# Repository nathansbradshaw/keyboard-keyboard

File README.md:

# Keyboard-keyboard

Keyboard-keyboard is a Hall-effect keyboard PCB. The design is based on the IBM Model M keyboard layout. But this is intended to be used as a gimicky musical keyboard.

## Acknowledgements

- Based on the work of 
  [peppapighs](https://github.com/peppapighs/HE60/tree/main) for the hall effect keyboard and [dcpedit](https://github.com/dcpedit/mod-mmm) for the Model M layout.

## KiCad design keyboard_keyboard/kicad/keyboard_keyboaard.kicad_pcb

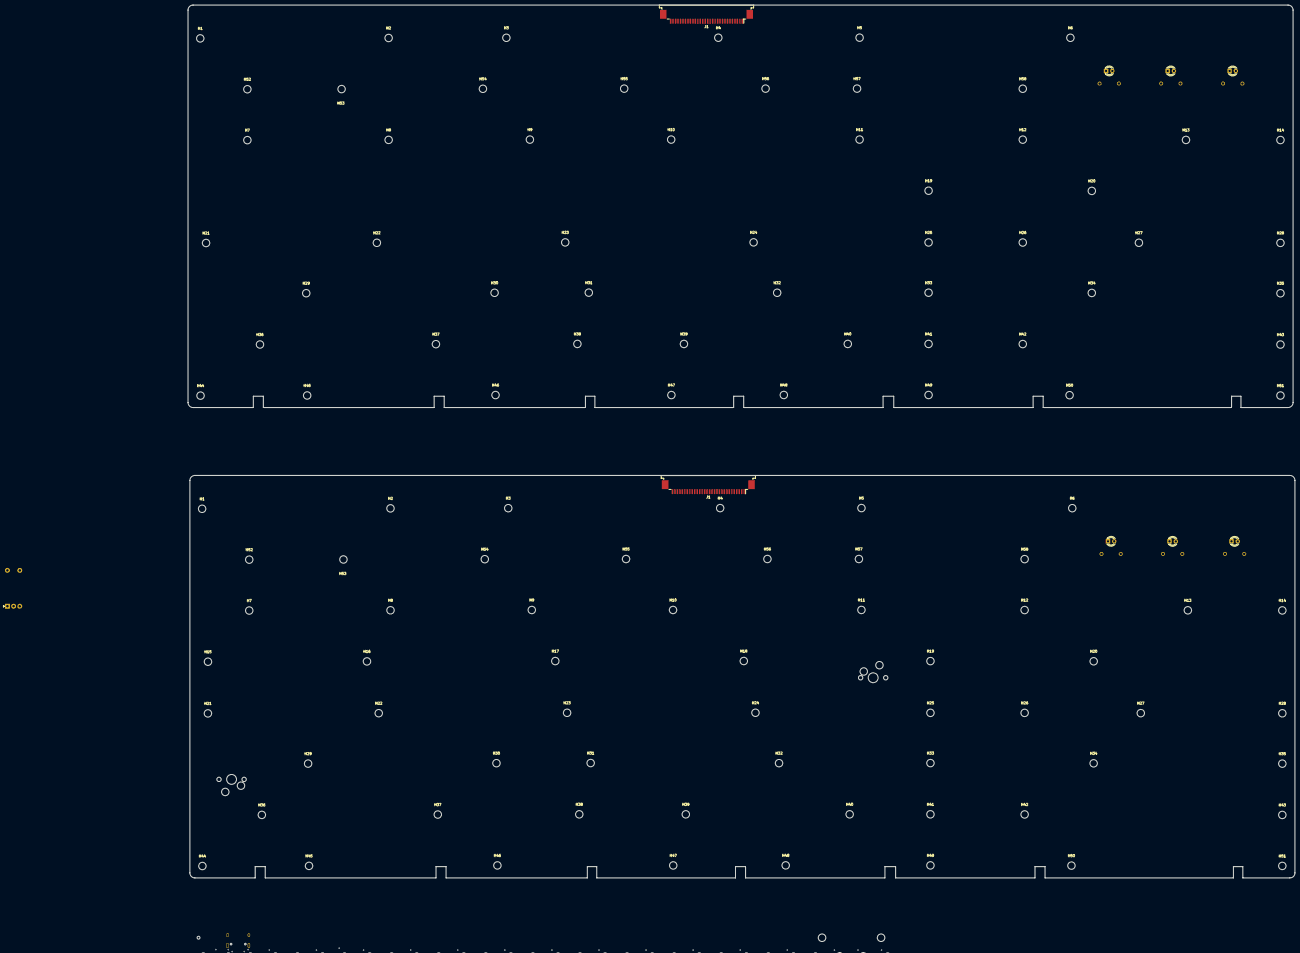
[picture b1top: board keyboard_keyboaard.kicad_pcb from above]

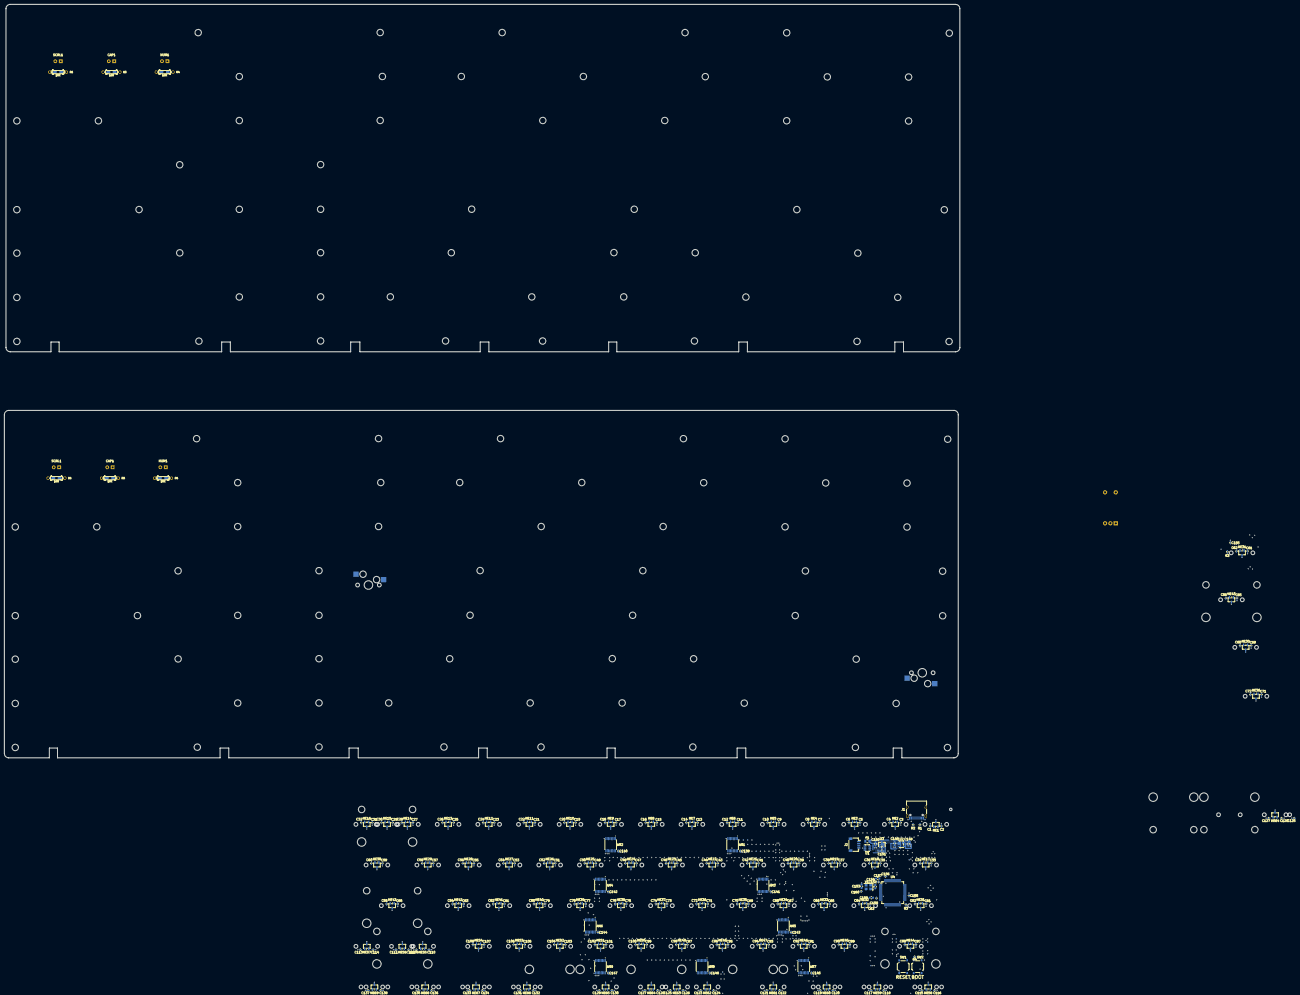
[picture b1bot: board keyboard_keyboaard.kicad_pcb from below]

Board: 2 copper layers, 447.8 x 353.1 mm, 484 parts (270 on the bottom side), 128 nets, no tracks yet.

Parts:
AM1, AM2, AM3, AM4, AM5, AM6, AM7, AM8, AM9: SN74LV4051A; TSSOP-16_4.4x5mm_P0.65mm
C1, C3, C5, C7, C9, C11, C13, C15, C17, C19, C21, C23, C25, C27, C29, C31, C33, C35, C37, C39, C41, C43, C45, C47, C49, C51, C53, C55, C57, C59, C59#2, C61, C61#2, C63, C65, C67, C69, C71, C71#2, C73, C75, C77, C79, C81, C83, C85, C85#2, C87, C89, C91, C93, C95, C97, C99, C101, C103, C105, C107, C109, C111, C113, C115, C117, C119, C121, C123, C125, C125#2, C127, C127#2, C129, C131, C133, C135, C137, C139, C140, C141, C142, C143, C144, C145, C146, C147, C154, C155, C155#2, C156, C158, C160: 100n; C_0402_1005Metric
C2, C4, C6, C8, C10, C12, C14, C16, C18, C20, C22, C24, C26, C28, C30, C32, C34, C36, C38, C40, C42, C44, C46, C48, C50, C52, C54, C56, C58, C60, C60#2, C62, C62#2, C64, C66, C68, C70, C72, C72#2, C74, C76, C78, C80, C82, C84, C86, C86#2, C88, C90, C92, C94, C96, C98, C100, C102, C104, C106, C108, C110, C112, C114, C116, C118, C120, C122, C124, C126, C128, C128#2, C130, C132, C134, C136, C138: 4.7n; C_0402_1005Metric
C148, C149, C150, C151: 2.2u; C_0603_1608Metric
C152, C153: 30p; C_0603_1608Metric
C157: 10u; C_0603_1608Metric
C159: 1u; C_0603_1608Metric
CAP1, CAP1#2: LED; LED_D3.0mm
F1: BSMD0805-050-24V; Fuse_0805_2012Metric
H1, H1#2, H2, H2#2, H3, H3#2, H4, H4#2, H5, H5#2, H6, H6#2, H7, H7#2, H8, H8#2, H9, H9#2, H10, H10#2, H11, H11#2, H12, H12#2, H13, H13#2, H14, H14#2, H15, H16, H17, H18, H19, H19#2, H20, H20#2, H21, H21#2, H22, H22#2, H23, H23#2, H24, H24#2, H25, H25#2, H26, H26#2, H27, H27#2, H28, H28#2, H29, H29#2, H30, H30#2, H31, H31#2, H32, H32#2, H33, H33#2, H34, H34#2, H35, H35#2, H36, H36#2, H37, H37#2, H38, H38#2, H39, H39#2, H40, H40#2, H41, H41#2, H42, H42#2, H43, H43#2, H44, H44#2, H45, H45#2, H46, H46#2, H47, H47#2, H48, H48#2, H49, H49#2, H50, H50#2, H51, H51#2, H52, H52#2, H53, H53#2, H54, H54#2, H55, H55#2, H56, H56#2, H57, H57#2, H58, H58#2: MountingHole; MountingHole_3mm
HE1, HE2, HE3, HE4, HE5, HE6, HE7, HE8, HE9, HE10, HE11, HE12, HE13, HE14, HE15, HE16, HE17, HE18, HE19, HE20, HE21, HE22, HE23, HE24, HE25, HE26, HE27, HE28, HE29, HE30, HE30#2, HE31, HE31#2, HE32, HE33, HE34, HE35, HE36, HE36#2, HE37, HE38, HE39, HE40, HE41, HE42, HE43, HE43#2, HE44, HE45, HE46, HE47, HE48, HE49, HE50, HE51, HE52, HE53, HE54, HE55, HE56, HE57, HE58, HE59, HE60, HE61, HE62, HE63, HE64, HE64#2, HE65, HE66, HE67, HE68, HE69: MT9102ET; SOT-23-3
J1, J1#2: Conn_01x30; TE_3-84952-0_1x30-1MP_P1.0mm_Horizontal
J1#3: TYPE-C-31-M-12; USB_C_Receptacle_HRO_TYPE-C-31-M-12
J2: JST_SH; JST_SH_SM04B-SRSS-TB_1x04-1MP_P1.00mm_Horizontal
MX1, MX2, MX3, MX4, MX5, MX6, MX7, MX8, MX9, MX10, MX11, MX12, MX13, MX14, MX16, MX18, MX19, MX20, MX21, MX22, MX23, MX24, MX25, MX26, MX27, MX28, MX29, MX32, MX33, MX34, MX35, MX36, MX36#2, MX37, MX38, MX39, MX40, MX41, MX42, MX45, MX46, MX47, MX48, MX49, MX50, MX51, MX52, MX53, MX54, MX57, MX61, MX64, MX69, MX73: 1U; MX-1U
MX15: 2U; MX-2U
MX17, MX30, MX30#2, MX59, MX63, MX71, MX75: 1.5U; MX-1.5U
MX31, MX31#2, MX55: 1.75U; MX-1.75U
MX040: MX-NoLED; MXOnly-1.25U-Hotswap
MX43, MX43#2, MX44: 2.25U; MX-2.25U
MX56: 2.75U; MX-2.75U
MX58, MX60, MX62, MX70, MX72, MX74, MX76: 1.25U; MX-1.25U
MX65: 2.25U; MX-2.25U-ReversedStabilizers
MX66, MX66#2: 6.25U; MX-6.25U-ReversedStabilizers
MX67, MX67#2: 7U; MX-7U-ReversedStabilizers
MX68, MX68#2: 2.75U; MX-2.75U-ReversedStabilizers
MX086: MX-NoLED; MXOnly-1.5U-Hotswap
NUM1, NUM1#2: LED; LED_D3.0mm
R1, R2: 5.1k; R_0402_1005Metric
R3, R3#2, R4#3: 12k; R_0402_1005Metric
R4, R4#2, R5, R5#2, R6, R6#2: 10K; Resistor-Hybrid-Back
SCRL1, SCRL1#2: LED; LED_D3.0mm
SW1, SW2: TS-1187A-B-A-B; SW_Push_1P1T_XKB_TS-1187A
SWR3: RotaryEncoder_Switch; RotaryEncoder_EC11_Nonplated
TH1, TH2: ToolingHole
U1: USBLC6-2SC6; SOT-23-6
U2: TLV75733PDBV; SOT-23-5
U3: XC6206P332MR-G; SOT-23-3
U4: AT32F405RCT7; LQFP-64_10x10mm_P0.5mm
Y1: X322512MSB4SI; Crystal_SMD_3225-4Pin_3.2x2.5mm

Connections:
+3.3V: C151.1, C154.1, C155.1, C155#2.1, C156.1, C157.1, SW2.2, U3.2 (VO), U4.1 (VDD), U4.36 (VDD), U4.64 (VDD)
+3.3VA: AM1.16 (VDD), AM2.16 (VDD), AM3.16 (VDD), AM4.16 (VDD), AM5.16 (VDD), AM6.16 (VDD), AM7.16 (VDD), AM8.16 (VDD), AM9.16 (VDD), C1.1, C3.1, C5.1, C7.1, C9.1, C11.1, C13.1, C15.1, C17.1, C19.1, C21.1, C23.1, C25.1, C27.1, C29.1, C31.1, C33.1, C35.1, C37.1, C39.1, C41.1, C43.1, C45.1, C47.1, C49.1, C51.1, C53.1, C55.1, C57.1, C59.1, C59#2.1, C61.1, C61#2.1, C63.1, C65.1, C67.1, C69.1, C71.1, C71#2.1, C73.1, C75.1, C77.1, C79.1, C81.1, C83.1, C85.1, C85#2.1, C87.1, C89.1, C91.1, C93.1, C95.1, C97.1, C99.1, C101.1, C103.1, C105.1, C107.1, C109.1, C111.1, C113.1, C115.1, C117.1, C119.1, C121.1, C123.1, C125.1, C125#2.1, C127.1, C127#2.1, C129.1, C131.1, C133.1, C135.1, C137.1, C139.1, C140.1, C141.1, C142.1, C143.1, C144.1, C145.1, C146.1, C147.1, C149.1, C158.1, C159.1, HE1.1 (VCC), HE2.1 (VCC), HE3.1 (VCC), HE4.1 (VCC), HE5.1 (VCC), HE6.1 (VCC), HE7.1 (VCC), HE8.1 (VCC), HE9.1 (VCC), HE10.1 (VCC), HE11.1 (VCC), HE12.1 (VCC), HE13.1 (VCC), HE14.1 (VCC), HE15.1 (VCC), HE16.1 (VCC), HE17.1 (VCC), HE18.1 (VCC), HE19.1 (VCC), HE20.1 (VCC), HE21.1 (VCC), HE22.1 (VCC), HE23.1 (VCC), HE24.1 (VCC), HE25.1 (VCC), HE26.1 (VCC), HE27.1 (VCC), HE28.1 (VCC), HE29.1 (VCC), HE30.1 (VCC), HE30#2.1 (VCC), HE31.1 (VCC), HE31#2.1 (VCC), HE32.1 (VCC), HE33.1 (VCC), HE34.1 (VCC), HE35.1 (VCC), HE36.1 (VCC), HE36#2.1 (VCC), HE37.1 (VCC), HE38.1 (VCC), HE39.1 (VCC), HE40.1 (VCC), HE41.1 (VCC), HE42.1 (VCC), HE43.1 (VCC), HE43#2.1 (VCC), HE44.1 (VCC), HE45.1 (VCC), HE46.1 (VCC), HE47.1 (VCC), HE48.1 (VCC), HE49.1 (VCC), HE50.1 (VCC), HE51.1 (VCC), HE52.1 (VCC), HE53.1 (VCC), HE54.1 (VCC), HE55.1 (VCC), HE56.1 (VCC), HE57.1 (VCC), HE58.1 (VCC), HE59.1 (VCC), HE60.1 (VCC), HE61.1 (VCC), HE62.1 (VCC), HE63.1 (VCC), HE64.1 (VCC), HE64#2.1 (VCC), HE65.1 (VCC), HE66.1 (VCC), HE67.1 (VCC), HE68.1 (VCC), HE69.1 (VCC), U2.5 (OUT), U4.13 (VDDA)
+5V: C148.1, C150.1, F1.2, U1.5 (VBUS), U2.1 (IN), U2.3 (EN), U3.3 (VI)
BOOT0: R4#3.1, SW2.1, U4.60 (PF11/BOOT0)
CAPS_LED: CAP1.2 (A), CAP1#2.2 (A), J1.29, J1#2.29
COL0: J1.28, J1#2.28, MX040.1 (COL)
COL1: J1.27, J1#2.27
COL2: J1.26, J1#2.26
COL3: J1.23, J1#2.23
COL4: J1.22, J1#2.22
COL5: J1.11, J1#2.11
COL6: J1.10, J1#2.10, MX086.1 (COL)
COL7: J1.7, J1#2.7
COL8: J1.5, J1#2.5
COL9: J1.4, J1#2.4
GND: AM1.6 (Inh), AM1.7 (VEE), AM1.8 (VSS), AM1.12 (X3), AM2.6 (Inh), AM2.7 (VEE), AM2.8 (VSS), AM3.2 (X6), AM3.6 (Inh), AM3.7 (VEE), AM3.8 (VSS), AM4.6 (Inh), AM4.7 (VEE), AM4.8 (VSS), AM5.6 (Inh), AM5.7 (VEE), AM5.8 (VSS), AM5.15 (X2), AM6.6 (Inh), AM6.7 (VEE), AM6.8 (VSS), AM7.6 (Inh), AM7.7 (VEE), AM7.8 (VSS), AM8.6 (Inh), AM8.7 (VEE), AM8.8 (VSS), AM9.6 (Inh), AM9.7 (VEE), AM9.8 (VSS), C1.2, C2.2, C3.2, C4.2, C5.2, C6.2, C7.2, C8.2, C9.2, C10.2, C11.2, C12.2, C13.2, C14.2, C15.2, C16.2, C17.2, C18.2, C19.2, C20.2, C21.2, C22.2, C23.2, C24.2, C25.2, C26.2, C27.2, C28.2, C29.2, C30.2, C31.2, C32.2, C33.2, C34.2, C35.2, C36.2, C37.2, C38.2, C39.2, C40.2, C41.2, C42.2, C43.2, C44.2, C45.2, C46.2, C47.2, C48.2, C49.2, C50.2, C51.2, C52.2, C53.2, C54.2, C55.2, C56.2, C57.2, C58.2, C59.2, C59#2.2, C60.2, C60#2.2, C61.2, C61#2.2, C62.2, C62#2.2, C63.2, C64.2, C65.2, C66.2, C67.2, C68.2, C69.2, C70.2, C71.2, C71#2.2, C72.2, C72#2.2, C73.2, C74.2, C75.2, C76.2, C77.2, C78.2, C79.2, C80.2, C81.2, C82.2, C83.2, C84.2, C85.2, C85#2.2, C86.2, C86#2.2, C87.2, C88.2, C89.2, C90.2, C91.2, C92.2, C93.2, C94.2, C95.2, C96.2, C97.2, C98.2, C99.2, C100.2, C101.2, C102.2, C103.2, C104.2, C105.2, C106.2, C107.2, C108.2, C109.2, C110.2, C111.2, C112.2, C113.2, C114.2, C115.2, C116.2, C117.2, C118.2, C119.2, C120.2, C121.2, C122.2, C123.2, C124.2, C125.2, C125#2.2, C126.2, C127.2, C127#2.2, C128.2, C128#2.2, C129.2, C130.2, C131.2, C132.2, C133.2, C134.2, C135.2, C136.2, C137.2, C138.2, C139.2, C140.2, C141.2, C142.2, C143.2, C144.2, C145.2, C146.2, C147.2, C148.2, C149.2, C150.2, C151.2, C152.2, C153.2, C154.2, C155.2, C155#2.2, C156.2, C157.2, C158.2, C159.2, C160.2, HE1.3 (GND), HE2.3 (GND), HE3.3 (GND), HE4.3 (GND), HE5.3 (GND), HE6.3 (GND), HE7.3 (GND), HE8.3 (GND), HE9.3 (GND), HE10.3 (GND), HE11.3 (GND), HE12.3 (GND), HE13.3 (GND), HE14.3 (GND), HE15.3 (GND), HE16.3 (GND), HE17.3 (GND), HE18.3 (GND), HE19.3 (GND), HE20.3 (GND), HE21.3 (GND), HE22.3 (GND), HE23.3 (GND), HE24.3 (GND), HE25.3 (GND), HE26.3 (GND), HE27.3 (GND), HE28.3 (GND), HE29.3 (GND), HE30.3 (GND), HE30#2.3 (GND), HE31.3 (GND), HE31#2.3 (GND), HE32.3 (GND), HE33.3 (GND), HE34.3 (GND), HE35.3 (GND), HE36.3 (GND), HE36#2.3 (GND), HE37.3 (GND), HE38.3 (GND), HE39.3 (GND), HE40.3 (GND), HE41.3 (GND), HE42.3 (GND), HE43.3 (GND), HE43#2.3 (GND), HE44.3 (GND), HE45.3 (GND), HE46.3 (GND), HE47.3 (GND), HE48.3 (GND), HE49.3 (GND), HE50.3 (GND), HE51.3 (GND), HE52.3 (GND), HE53.3 (GND), HE54.3 (GND), HE55.3 (GND), HE56.3 (GND), HE57.3 (GND), HE58.3 (GND), HE59.3 (GND), HE60.3 (GND), HE61.3 (GND), HE62.3 (GND), HE63.3 (GND), HE64.3 (GND), HE64#2.3 (GND), HE65.3 (GND), HE66.3 (GND), HE67.3 (GND), HE68.3 (GND), HE69.3 (GND), J1.1, J1.30, J1#2.1, J1#2.30, J1#3.A1 (GND), J1#3.A12 (GND), J1#3.B1 (GND), J1#3.B12 (GND), J1#3.S1 (SHIELD), J2.4, R1.2, R2.1, R3.1, R3#2.1, R4.2, R4#2.2, R4#3.2, R5.2, R5#2.2, R6.2, R6#2.2, SW1.2, U1.2 (GND), U2.2 (GND), U3.1 (GND), U4.12 (VSSA), U4.31 (VSS), U4.63 (VSS), Y1.2, Y1.4
HE1: AM3.15 (X2), C2.1, HE1.2 (OUT)
HE2: AM1.15 (X2), C4.1, HE2.2 (OUT)
HE3: AM1.14 (X1), C6.1, HE3.2 (OUT)
HE4: AM1.13 (X0), C8.1, HE4.2 (OUT)
HE5: AM1.1 (X4), C10.1, HE5.2 (OUT)
HE6: AM1.2 (X6), C12.1, HE6.2 (OUT)
HE7: AM1.4 (X7), C14.1, HE7.2 (OUT)
HE8: AM1.5 (X5), C16.1, HE8.2 (OUT)
HE9: AM2.1 (X4), C18.1, HE9.2 (OUT)
HE10: AM2.2 (X6), C20.1, HE10.2 (OUT)
HE11: AM2.4 (X7), C22.1, HE11.2 (OUT)
HE12: AM2.5 (X5), C24.1, HE12.2 (OUT)
HE13: AM2.15 (X2), C26.1, HE13.2 (OUT)
HE14: AM2.14 (X1), C28.1, HE14.2 (OUT)
HE15: AM2.13 (X0), C30.1, HE15.2 (OUT)
HE16: AM2.12 (X3), C32.1, HE16.2 (OUT)
HE17: AM3.14 (X1), C34.1, HE17.2 (OUT)
HE18: AM3.13 (X0), C36.1, HE18.2 (OUT)
HE19: AM3.12 (X3), C38.1, HE19.2 (OUT)
HE20: AM3.1 (X4), C40.1, HE20.2 (OUT)
HE21: AM3.4 (X7), C42.1, HE21.2 (OUT)
HE22: AM3.5 (X5), C44.1, HE22.2 (OUT)
HE23: AM4.1 (X4), C46.1, HE23.2 (OUT)
HE24: AM4.2 (X6), C48.1, HE24.2 (OUT)
HE25: AM4.4 (X7), C50.1, HE25.2 (OUT)
HE26: AM4.5 (X5), C52.1, HE26.2 (OUT)
HE27: AM4.15 (X2), C54.1, HE27.2 (OUT)
HE28: AM4.14 (X1), C56.1, HE28.2 (OUT)
HE29: AM4.13 (X0), C58.1, HE29.2 (OUT)
HE30: AM4.12 (X3), C60.1, C60#2.1, HE30.2 (OUT), HE30#2.2 (OUT)
HE31: AM7.1 (X4), C62.1, C62#2.1, HE31.2 (OUT), HE31#2.2 (OUT)
HE32: AM5.1 (X4), C64.1, HE32.2 (OUT)
HE33: AM5.2 (X6), C66.1, HE33.2 (OUT)
HE34: AM5.4 (X7), C68.1, HE34.2 (OUT)
HE35: AM5.5 (X5), C70.1, HE35.2 (OUT)
HE36: AM5.14 (X1), C72.1, C72#2.1, HE36.2 (OUT), HE36#2.2 (OUT)
HE37: AM5.13 (X0), C74.1, HE37.2 (OUT)
HE38: AM5.12 (X3), C76.1, HE38.2 (OUT)
HE39: AM6.1 (X4), C78.1, HE39.2 (OUT)
HE40: AM6.2 (X6), C80.1, HE40.2 (OUT)
HE41: AM6.4 (X7), C82.1, HE41.2 (OUT)
HE42: AM6.5 (X5), C84.1, HE42.2 (OUT)
HE43: AM6.15 (X2), C86.1, C86#2.1, HE43.2 (OUT), HE43#2.2 (OUT)
HE44: AM7.2 (X6), C88.1, HE44.2 (OUT)
HE45: AM7.4 (X7), C90.1, HE45.2 (OUT)
HE46: AM7.5 (X5), C92.1, HE46.2 (OUT)
HE47: AM8.1 (X4), C94.1, HE47.2 (OUT)
HE48: AM8.2 (X6), C96.1, HE48.2 (OUT)
HE49: AM8.4 (X7), C98.1, HE49.2 (OUT)
HE50: AM8.5 (X5), C100.1, HE50.2 (OUT)
HE51: AM9.1 (X4), C102.1, HE51.2 (OUT)
HE52: AM9.2 (X6), C104.1, HE52.2 (OUT)
HE53: AM9.4 (X7), C106.1, HE53.2 (OUT)
HE54: AM9.5 (X5), C108.1, HE54.2 (OUT)
HE55: AM6.12 (X3), C110.1, HE55.2 (OUT)
HE56: AM6.13 (X0), C112.1, HE56.2 (OUT)
HE57: AM6.14 (X1), C114.1, HE57.2 (OUT)
HE58: AM7.15 (X2), C116.1, HE58.2 (OUT)
HE59: AM7.14 (X1), C118.1, HE59.2 (OUT)
HE60: AM7.13 (X0), C120.1, HE60.2 (OUT)
HE61: AM7.12 (X3), C122.1, HE61.2 (OUT)
HE62: AM8.12 (X3), C124.1, HE62.2 (OUT)
HE63: AM8.13 (X0), C126.1, HE63.2 (OUT)
HE64: AM8.14 (X1), C128.1, C128#2.1, HE64.2 (OUT), HE64#2.2 (OUT)
HE65: AM8.15 (X2), C130.1, HE65.2 (OUT)
HE66: AM9.12 (X3), C132.1, HE66.2 (OUT)
HE67: AM9.13 (X0), C134.1, HE67.2 (OUT)
HE68: AM9.14 (X1), C136.1, HE68.2 (OUT)
HE69: AM9.15 (X2), C138.1, HE69.2 (OUT)
HEXT_IN: C152.1, U4.5 (PF0/HEXT_IN), Y1.1
HEXT_OUT: C153.1, U4.6 (PF1/HEXT_OUT), Y1.3
MUX_OUT_1: AM1.3 (X), U4.17 (PA3)
MUX_OUT_2: AM2.3 (X), U4.20 (PA4)
MUX_OUT_3: AM3.3 (X), U4.21 (PA5)
MUX_OUT_4: AM4.3 (X), U4.22 (PA6)
MUX_OUT_5: AM5.3 (X), U4.23 (PA7)
MUX_OUT_6: AM6.3 (X), U4.24 (PC4)
MUX_OUT_7: AM7.3 (X), U4.25 (PC5)
MUX_OUT_8: AM8.3 (X), U4.26 (PB0)
MUX_OUT_9: AM9.3 (X), U4.27 (PB1)
MUX_SELECT_0: AM1.11 (A), AM2.11 (A), AM3.11 (A), AM4.11 (A), AM5.11 (A), AM6.11 (A), AM7.11 (A), AM8.11 (A), AM9.11 (A), U4.9 (PC1)
MUX_SELECT_1: AM1.10 (B), AM2.10 (B), AM3.10 (B), AM4.10 (B), AM5.10 (B), AM6.10 (B), AM7.10 (B), AM8.10 (B), AM9.10 (B), U4.10 (PC2)
MUX_SELECT_2: AM1.9 (C), AM2.9 (C), AM3.9 (C), AM4.9 (C), AM5.9 (C), AM6.9 (C), AM7.9 (C), AM8.9 (C), AM9.9 (C), U4.11 (PC3)
NRST: C160.1, SW1.1, U4.7 (NRST)
NUM_LED: J1.3, J1#2.3, NUM1.2 (A), NUM1#2.2 (A)
unnamed: CAP1.1 (K), CAP1#2.1 (K), R5.1, R5#2.1
unnamed: J1#3.A5 (CC1), R1.1
unnamed: J1#3.B5 (CC2), R2.2
unnamed: NUM1.1 (K), NUM1#2.1 (K), R4.1, R4#2.1
unnamed: R6.1, R6#2.1, SCRL1.1 (K), SCRL1#2.1 (K)
unnamed: R3.2, R3#2.2, U4.33 (OTGHS1_R)
RE1: J1.9, J1#2.9
RE2: J1.8, J1#2.8
RE3: J1.6, J1#2.6
ROW0: J1.25, J1#2.25
ROW1: J1.21, J1#2.21
ROW2: J1.20, J1#2.20
ROW3: J1.19, J1#2.19
ROW4: J1.18, J1#2.18
ROW5: J1.17, J1#2.17
ROW6: J1.24, J1#2.24
ROW7: J1.16, J1#2.16
ROW8: J1.15, J1#2.15
ROW9: J1.14, J1#2.14
ROW10: J1.13, J1#2.13
ROW11: J1.12, J1#2.12
SCRL_LED: J1.2, J1#2.2, SCRL1.2 (A), SCRL1#2.2 (A)
USB_D+: U1.4 (I/O2), U4.35 (OTGHS1_D+)
USB_D-: U1.6 (I/O1), U4.34 (OTGHS1_D-)
USB_PLUG_D+: J1#3.A6 (D+), J1#3.B6 (D+), J2.3, U1.3 (I/O2)
USB_PLUG_D-: J1#3.A7 (D-), J1#3.B7 (D-), J2.2, U1.1 (I/O1)
VBUS: F1.1, J1#3.A4 (VBUS), J1#3.A9 (VBUS), J1#3.B4 (VBUS), J1#3.B9 (VBUS), J2.1

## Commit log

2025-12-31 init
2025-12-31 move readme up
2026-02-07 chore: move files
2026-02-12 init hall effect code
2026-02-12 use correct pin
2026-02-12 slow key press scans
2026-02-12 keyboard velocity thing
2026-02-13 wip: midi sender
2026-02-13 feat: better button debouncing
